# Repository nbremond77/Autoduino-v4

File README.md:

# Autoduino

Arduino DUE shield to interface the I/O modules of A4 Technology // Autoduino est un bouclier pour Arduino DUE qui permet de piloter les maquettes A4 Technology utilisées pour l'enseignement de la technologie. Il permet également d'interfacer des module Grove.

La face "Bottom":

La face "Top"

Exemples de maquettes A4:

http://www.a4.fr/maquette-motorisee-programmable-portail-1-battant-version-kit.html

http://www.a4.fr/banc-d-essai-eclairage-domestique-autolumi-version-kit.html

http://www.a4.fr/autoalarme-maquette-experimentale-d-un-systeme-d-alarme-kit.html

Vous trouverez sur ce site, les fichiers relatif à la carte électronique, et les développements logiciels associés, dès qu'ils seront disponibles. Cette carte peut être programmée en utilisant l'environnement Arduino. Mais elle peut également en programmée avec Blockly@rDuino, l'excellent projet de Sébastien Canet:

http://technologiescollege.github.io/Blockly-at-rduino/

https://github.com/technologiescollege/Blockly-at-rduino

# Introduction
Le bouclier Autoduino permet de piloter les maquettes A4 technology grâce à un Arduino DUE. Pour cela, le bouclier est équipé de 
- 14 connecteurs Jack 2.5mm permettant la connection des capteurs et actionneurs des maquette A4, équipé de LED pour indiquer l'état de l'entrée ou de la sortie. Des connecteurs Grove (4 broches) sont également prévus, et connectés aux mêmes entrées sorties (voir le schéma pour les détails). Les entrées sont équipées de résistances "Pull-Up" c'est à dire reliées à l'alimentation positive. Les entrées et sorties sont universelles (les schémas sont identiques), les 14 connections peuvent entre utilisées en entrée ou en sortie.
- 2 connecteurs jack 2.5mm pour deux moteurs DC, également complétés par des connecteurs Grove.
- 2 LED RGB adressables (type WS2812B),
- 1 encodeur/push,
- quelques connecteurs supplémentaires permettant de connecter des capteurs/actionneurs plus évolués (I2C, SPI, CAN, Serial...),
- 1 connecteur pour un module BlueTooth,
- 1 convertisseur Step/Up permettant d'alimenter la carte et l'Arduino avec deux piles de 1.5V, ou avec un accumulateur 3.7V,
- 1 connecteur pour un écran graphique couleur tactile de 2.8" connecté en SPI référencé TJCTM24028-SPI disponible pour un prix raisonnable sur Aliexpress.com.

Pour supporter le grand nombre d'entrées/sorties, il a été nécessaire d'utiliser un Arduino plus complet que le UNO. Nous avons choisi le Arduino DUE qui est équipé d'un processeur 32 bits permettant d'héberger des programmes trés complexes.

# Spécificités de l'Arduino DUE

L'Arduino DUE fonctionne en 3.3V, et n'est pas compatible avec des périphériques fonctionnant en 5V. Assurez vous que les périphériques utilisés fonctionnent bien en 3.3V. Les deux interface moteur prévues sur la carte Autoduino sont quant-à-elles alimentées en 5V.

# Schéma électronique

La conception du circuit imprimé a été réalisée avec kiCad, l'excellent logiciel de conception électronique, libre et multiplateforme. Le schéma est disponible ici:
https://github.com/nbremond77/Autoduino-v4/raw/master/Hardware/rev%204/Output/Autoduino-rev4.pdf

# Approvisionnement des composants

Les composants ont été achetés sur Aliepxress, et le PCb a été commandé chez PCBWay.com.

Voici des liens vers les principales références:

La carte Arduino DUE: https://fr.aliexpress.com/item/Free-shipping-Due-R3-ARM-Version-Main-Control-Board-with-usb-cable-for-arduino/32458422375.html?spm=2114.06010108.3.9.xlUYYH&ws_ab_test=searchweb0_0,searchweb201602_2_10152_10065_10151_10068_10305_10304_10306_10136_10137_10060_10302_10155_10062_437_10154_10056_5210020_10055_10054_10059_303_5290020_100031_10099_10103_10102_10096_10052_10053_10050_10107_10142_10051_5280011_10084_10083_10080_10082_10081_5260020_5270020_10177_5320020_10110_519_10111_10112_10113_10114_10182_10184_10078_10079_5240020_5230020_10073_10123_5250020_10189_142,searchweb201603_49,ppcSwitch_5&btsid=a1133e54-5694-44cb-906c-6a8b10082eb8&algo_expid=972c692f-a693-491d-9626-1f7036225856-1&algo_pvid=972c692f-a693-491d-9626-1f7036225856

Les connecteurs Jack 2.5mm CMS ref. PJ-242 : https://fr.aliexpress.com/item/500pcs-lot-PJ-242-6P-SMT-2-5MM-Female-Audio-Headphone-Jack-2-5MM-Dual-Track/32344264172.html?spm=2114.13010608.0.0.wAqt4l

L'écran LCD couleur tactile de 2.8" (attention, certains modèle ne sont pas équipés de l'interface tactile) : https://fr.aliexpress.com/item/2-8-Inch-240x320-Serial-Port-SPI-TFT-Screen-LCD-with-Touch-Screen-Panel-PCB-Board/32617643223.html?spm=2114.13010208.99999999.270.1LTJxa

Le module BlueTooth HC05 (les broches devront peut-être être déssoudées et remplacées par des barettes droites soudées sur la face inférieure) : https://fr.aliexpress.com/item/HC05-HC-05-master-slave-6pin-JY-MCU-anti-reverse-integrated-Bluetooth-serial-pass-through-module/32788718239.html?spm=2114.06010108.3.58.m5KIcO&ws_ab_test=searchweb0_0,searchweb201602_2_10152_10065_10151_10068_10305_10304_10306_10136_10137_10060_10302_10155_10062_437_10154_10056_5210020_10055_10054_10059_303_5290020_100031_10099_10103_10102_10096_10052_10053_10050_10107_10142_10051_5280011_10084_10083_10080_10082_10081_5260020_5270020_10177_5320020_10110_519_10111_10112_10113_10114_10182_10184_10078_10079_5240020_5230020_10073_10123_5250020_10189_142-10050,searchweb201603_49,ppcSwitch_5&btsid=7052be95-a9a1-4971-bb41-739faffda7ad&algo_expid=dd608b64-cccf-44a9-9c7e-1e9cdb78854b-7&algo_pvid=dd608b64-cccf-44a9-9c7e-1e9cdb78854b

Les autres composants sont des modèles standards.

# Circuit imprimé et fabrication

Autoduino utilise des composants CMS et des composants traversants. Le cuircuit imprimé fait 100x100mm et est du type double-face à trous métalisés. Nous l'avons fait fariqué chez PCBWay.com à un prix trés compétitif. Tous les fichiers nécessaires à sa fabrication sont dans le répertoire Output/Manufacturing (voir le fichier .Zip dans ce répertoire). Pensez également à commander un "Stencyl" pour la face "Bottom". Le Stencyl est un feuille de métal performée au laser au niveau des pastilles de soudure, et qui permet de grandement faciliter l'application de la pate à braser utilisée pour souder les  composants CMS.

Pour l'assemblage, de nombreux composants sont "montés en surface (CMS) sur la face "Bottom". Nous avons utilisé le Stencyl pour appliquer la pate à braser, positionné les composants CMS sur la carte, et passé la carte aisni équipé dans un four à refusion fait "maison" (plusieurs projets sont disponibles sur le web...).
Le montage des composants traversants, et des 2 LED sur la face "Top" se fait manuellement, aprés la refusion et le refroidissement de la carte. Cette méthode permet de réaliser plusieurs exemplaires de la carte en un temps raisonnable.

# Programmation
La programmation de l'Arduino peut se faire grâce à blockly@rDuino: http://technologiescollege.github.io/ en utilisant les blocs Grove par exemple.

http://technologiescollege.github.io/Blockly-at-rduino/

https://github.com/technologiescollege/Blockly-at-rduino

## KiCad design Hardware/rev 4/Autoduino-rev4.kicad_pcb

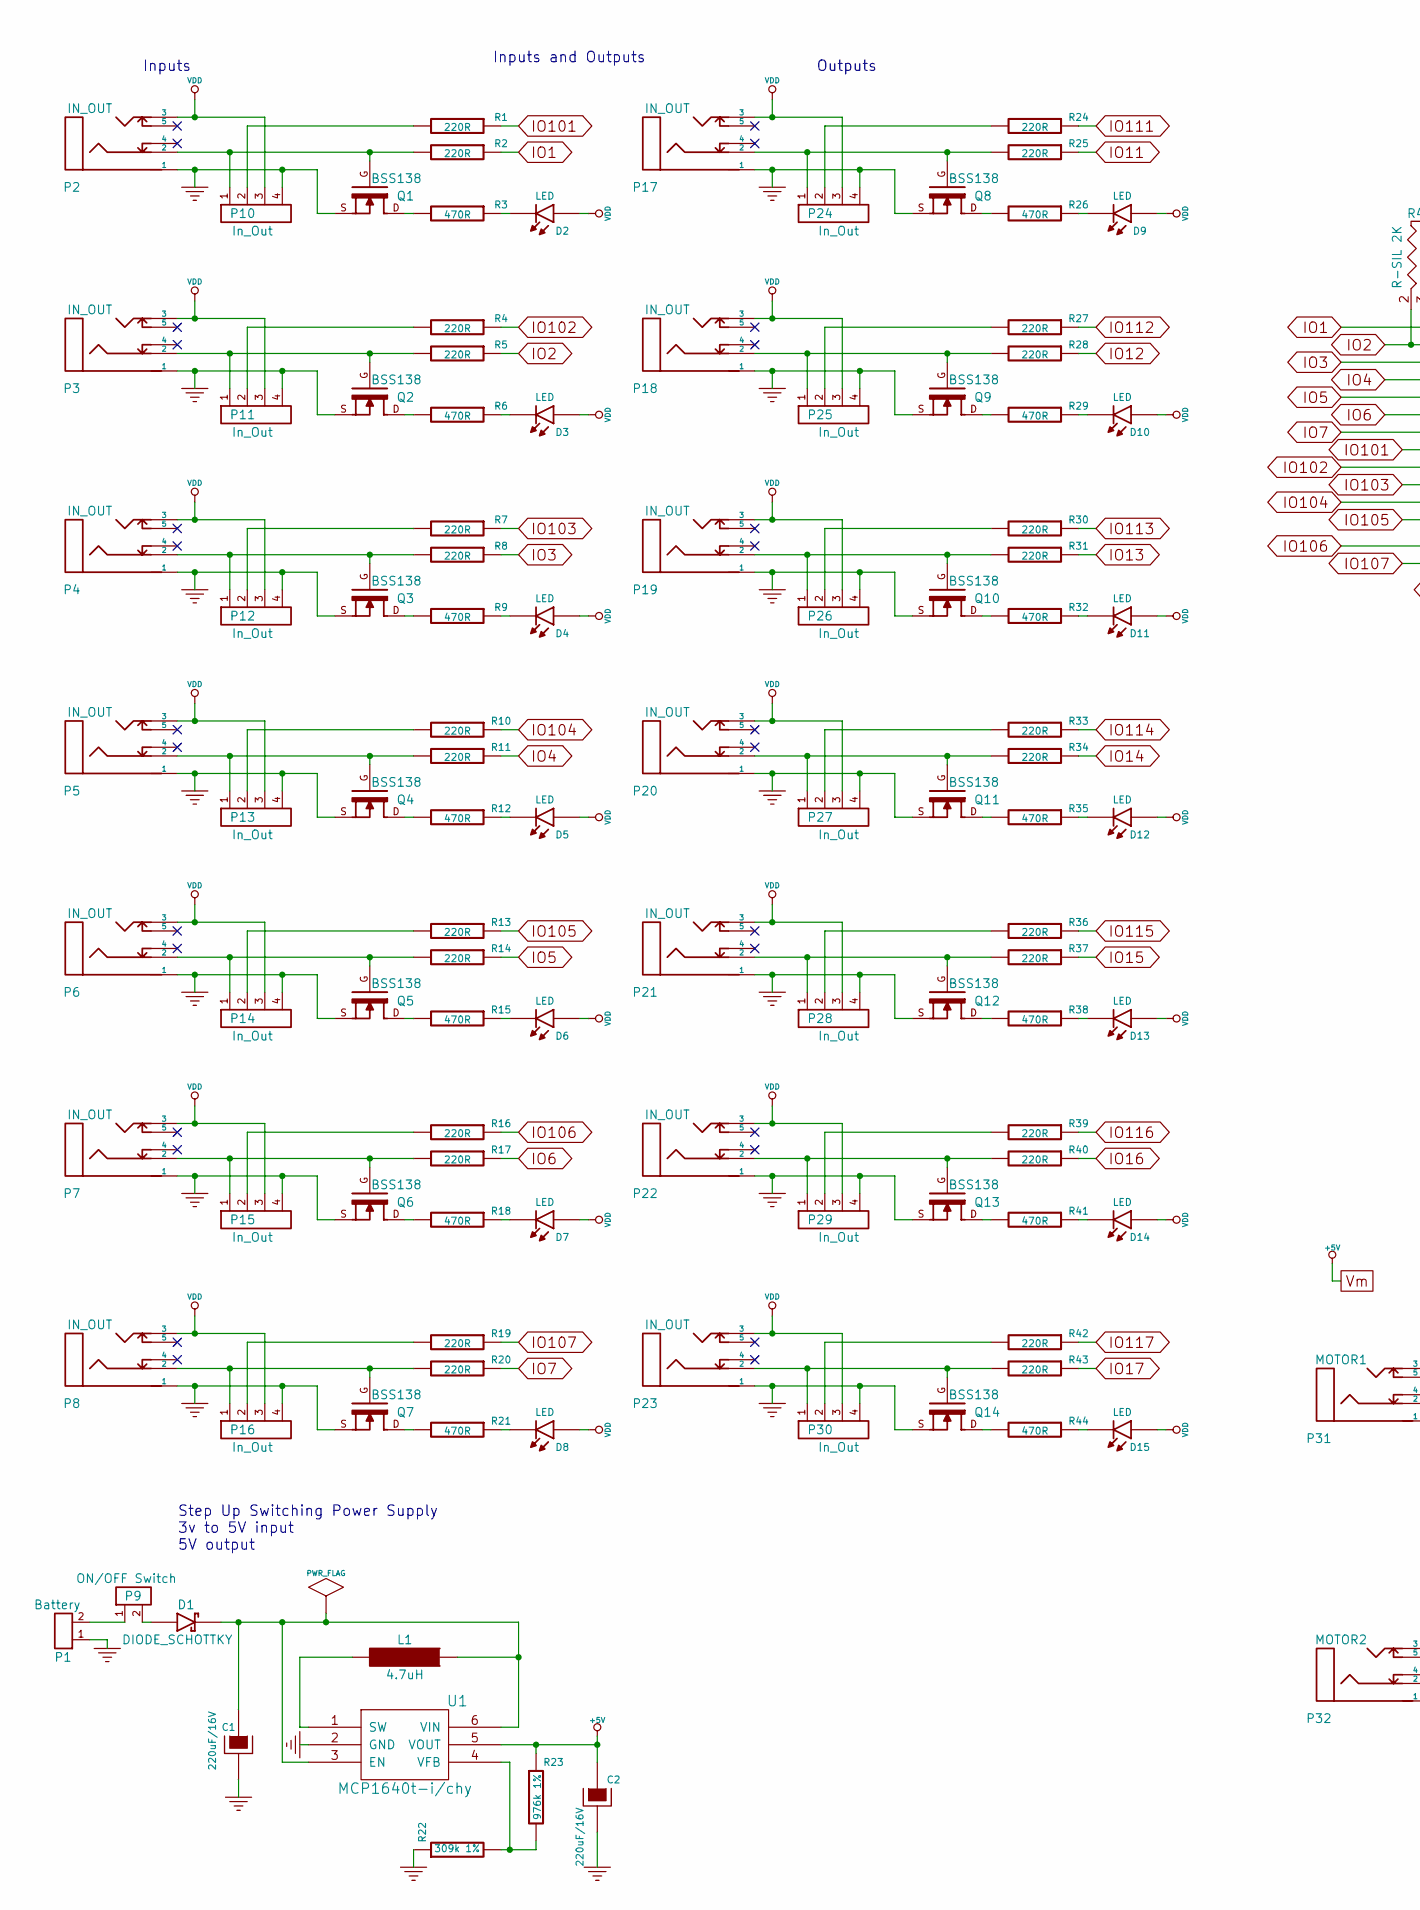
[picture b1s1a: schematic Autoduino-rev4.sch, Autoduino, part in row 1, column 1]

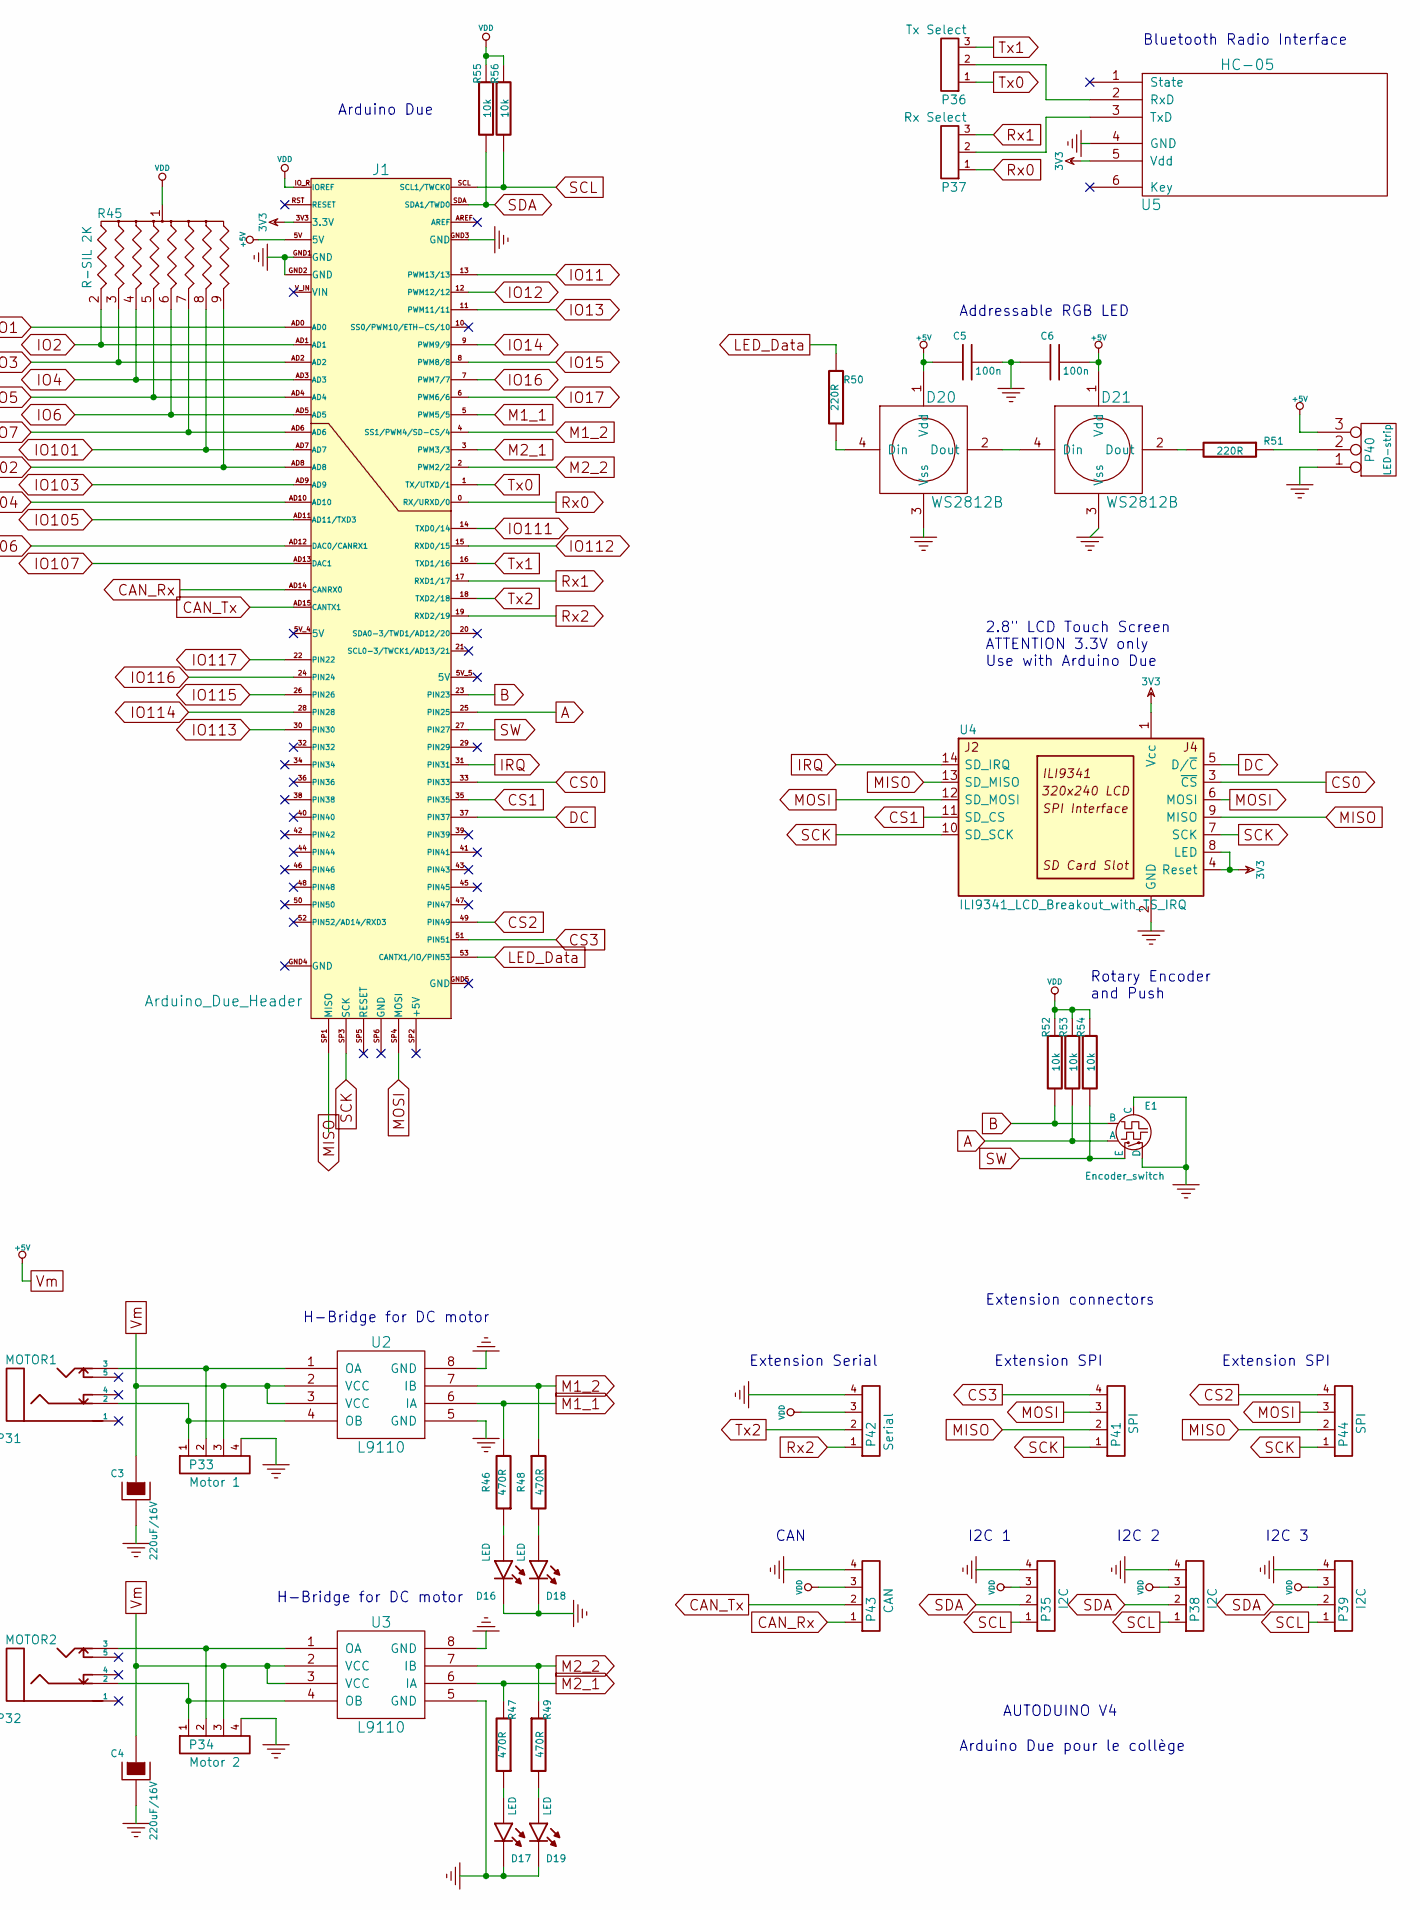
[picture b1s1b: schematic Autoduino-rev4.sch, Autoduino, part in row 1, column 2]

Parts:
C1, C2, C3, C4: 220uF/16V; CP_Elec_8x10
C5, C6: 100n; C_0805_HandSoldering
D1: DIODE_SCHOTTKY; D_MiniMELF_Handsoldering
D2, D3, D4, D5, D6, D7, D8, D9, D10, D11, D12, D13, D14, D15, D16, D17, D18, D19: LED; LED_D3.0mm
D20, D21: WS2812B; LED_WS2812B-PLCC4
E1: Encoder_switch; encoder_alps-ec12d
J1: Arduino_Due_Header; ARDUINO_MEGA_SHIELD
L1: 4.7uH; INDUCTOR_V
P1: Battery; Pin_Header_Straight_1x02_Pitch2.54mm
P2, P3, P4, P5, P6, P7, P8, P17, P18, P19, P20, P21, P22, P23: IN_OUT; 3.5mm_stereo_jack_PJ242_NBR
P9: ON/OFF Switch; Pin_Header_Straight_1x02_Pitch2.54mm
P10, P11, P12, P13, P14, P15, P16, P24, P25, P26, P27, P28, P29, P30: In_Out; Molex_MicroLatch-53253-0470_04x2.00mm_Straight
P31: MOTOR1; 3.5mm_stereo_jack_PJ242_NBR
P32: MOTOR2; 3.5mm_stereo_jack_PJ242_NBR
P33: Motor 1; Molex_MicroLatch-53253-0470_04x2.00mm_Straight
P34: Motor 2; Molex_MicroLatch-53253-0470_04x2.00mm_Straight
P35, P38, P39: I2C; Molex_MicroLatch-53253-0470_04x2.00mm_Straight
P36: Tx Select; Pin_Header_Straight_1x03_Pitch2.54mm
P37: Rx Select; Pin_Header_Straight_1x03_Pitch2.54mm
P40: LED-strip; Pin_Header_Straight_1x03_Pitch2.54mm
P41, P44: SPI; Molex_MicroLatch-53253-0470_04x2.00mm_Straight
P42: Serial; Molex_MicroLatch-53253-0470_04x2.00mm_Straight
P43: CAN; Molex_MicroLatch-53253-0470_04x2.00mm_Straight
Q1, Q2, Q3, Q4, Q5, Q6, Q7, Q8, Q9, Q10, Q11, Q12, Q13, Q14: BSS138; SOT23_FET
R1, R2, R4, R5, R7, R8, R10, R11, R13, R14, R16, R17, R19, R20, R24, R25, R27, R28, R30, R31, R33, R34, R36, R37, R39, R40, R42, R43, R50, R51: 220R; R_0805_HandSoldering
R3, R6, R9, R12, R15, R18, R21, R26, R29, R32, R35, R38, R41, R44, R46, R47, R48, R49: 470R; R_0805_HandSoldering
R22: 309k 1%; R_0805_HandSoldering
R23: 976k 1%; R_0805_HandSoldering
R45: R-SIL 2K; R_Array_SIP9
R52, R53, R54, R55, R56: 10k; R_0805_HandSoldering
U1: MCP1640t-i/chy; SOT-23-6_Handsoldering
U2, U3: L9110; SOIC-8_3.9x4.9mm_Pitch1.27mm
U4: ILI9341_LCD_Breakout_with_TS_IRQ; LCD_2.8_Touch_screen
U5: HC-05; Pin_Header_Angled_1x06_Pitch2.54mm

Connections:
3V3: J1.3V3 (3.3V), U4.1 (Vcc), U4.4 (Reset), U4.8 (LED), U5.5 (Vdd)
A: E1.1 (A), J1.25 (PIN25), R53.2
B: E1.3 (B), J1.23 (PIN23), R52.2
CAN_Rx: J1.AD14 (CANRX0), P43.1
CAN_Tx: J1.AD15 (CANTX1), P43.2
CS0: J1.33 (PIN33), U4.3 (~CS)
CS1: J1.35 (PIN35), U4.11 (SD_CS)
CS2: J1.49 (PIN49), P44.4
CS3: J1.51 (PIN51), P41.4
DC: J1.37 (PIN37), U4.5 (D/~C)
GND: C1.2, C2.2, C3.2, C4.2, C5.2, C6.1, D16.2 (K), D17.2 (K), D18.2 (K), D19.2 (K), D20.3 (Vss), D21.3 (Vss), E1.2 (C), E1.5 (D), J1.GND1 (GND), J1.GND2 (GND), J1.GND3 (GND), P1.1, P2.1, P3.1, P4.1, P5.1, P6.1, P7.1, P8.1, P10.4, P11.4, P12.4, P13.4, P14.4, P15.4, P16.4, P17.1, P18.1, P19.1, P20.1, P21.1, P22.1, P23.1, P24.4, P25.4, P26.4, P27.4, P28.4, P29.4, P30.4, P33.4, P34.4, P35.4, P38.4, P39.4, P40.1, P42.4, P43.4, Q1.S, Q2.S, Q3.S, Q4.S, Q5.S, Q6.S, Q7.S, Q8.S, Q9.S, Q10.S, Q11.S, Q12.S, Q13.S, Q14.S, R22.1, U1.2 (GND), U2.5 (GND), U2.8 (GND), U3.5 (GND), U3.8 (GND), U4.2 (GND), U5.4 (GND)
IO1: J1.AD0, R2.1
IO2: J1.AD1, R5.1, R45.2
IO3: J1.AD2, R8.1, R45.3
IO4: J1.AD3, R11.1, R45.4
IO5: J1.AD4, R14.1, R45.5
IO6: J1.AD5, R17.1, R45.6
IO7: J1.AD6, R20.1, R45.7
IO11: J1.13 (PWM13/13), R25.1
IO12: J1.12 (PWM12/12), R28.1
IO13: J1.11 (PWM11/11), R31.1
IO14: J1.9 (PWM9/9), R34.1
IO15: J1.8 (PWM8/8), R37.1
IO16: J1.7 (PWM7/7), R40.1
IO17: J1.6 (PWM6/6), R43.1
IO101: J1.AD7, R1.1, R45.8
IO102: J1.AD8, R4.1, R45.9
IO103: J1.AD9, R7.1
IO104: J1.AD10, R10.1
IO105: J1.AD11 (AD11/TXD3), R13.1
IO106: J1.AD12 (DAC0/CANRX1), R16.1
IO107: J1.AD13 (DAC1), R19.1
IO111: J1.14 (TXD0/14), R24.1
IO112: J1.15 (RXD0/15), R27.1
IO113: J1.30 (PIN30), R30.1
IO114: J1.28 (PIN28), R33.1
IO115: J1.26 (PIN26), R36.1
IO116: J1.24 (PIN24), R39.1
IO117: J1.22 (PIN22), R42.1
IRQ: J1.31 (PIN31), U4.14 (SD_IRQ)
LED_Data: J1.53 (CANTX1/IO/PIN53), R50.2
M1_1: J1.5 (PWM5/5), R46.2, U2.6 (IA)
M1_2: J1.4 (SS1/PWM4/SD-CS/4), R48.1, U2.7 (IB)
M2_1: J1.3 (PWM3/3), R47.2, U3.6 (IA)
M2_2: J1.2 (PWM2/2), R49.1, U3.7 (IB)
MISO: J1.SP1 (MISO), P41.2, P44.2, U4.9 (MISO), U4.13 (SD_MISO)
MOSI: J1.SP4 (MOSI), P41.3, P44.3, U4.6 (MOSI), U4.12 (SD_MOSI)
unnamed: C1.1, D1.2 (K), L1.1, U1.3 (EN), U1.6 (VIN)
unnamed: D1.1 (A), P9.2
unnamed: D2.2 (K), R3.1
unnamed: D3.2 (K), R6.1
unnamed: D4.2 (K), R9.1
unnamed: D5.2 (K), R12.1
unnamed: D6.2 (K), R15.1
unnamed: D7.2 (K), R18.1
unnamed: D8.2 (K), R21.1
unnamed: D9.2 (K), R26.1
unnamed: D10.2 (K), R29.1
unnamed: D11.2 (K), R32.1
unnamed: D12.2 (K), R35.1
unnamed: D13.2 (K), R38.1
unnamed: D14.2 (K), R41.1
unnamed: D15.2 (K), R44.1
unnamed: D16.1 (A), R46.1
unnamed: D17.1 (A), R47.1
unnamed: D18.1 (A), R48.2
unnamed: D19.1 (A), R49.2
unnamed: D20.2 (Dout), D21.4 (Din)
unnamed: D20.4 (Din), R50.1
unnamed: D21.2 (Dout), R51.2
unnamed: L1.2, U1.1 (SW)
unnamed: P1.2, P9.1
unnamed: P2.2, P10.1, Q1.G, R2.2
unnamed: P10.2, R1.2
unnamed: P3.2, P11.1, Q2.G, R5.2
unnamed: P11.2, R4.2
unnamed: P4.2, P12.1, Q3.G, R8.2
unnamed: P12.2, R7.2
unnamed: P5.2, P13.1, Q4.G, R11.2
unnamed: P13.2, R10.2
unnamed: P6.2, P14.1, Q5.G, R14.2
unnamed: P14.2, R13.2
unnamed: P7.2, P15.1, Q6.G, R17.2
unnamed: P15.2, R16.2
unnamed: P8.2, P16.1, Q7.G, R20.2
unnamed: P16.2, R19.2
unnamed: P17.2, P24.1, Q8.G, R25.2
unnamed: P18.2, P25.1, Q9.G, R28.2
unnamed: P19.2, P26.1, Q10.G, R31.2
unnamed: P20.2, P27.1, Q11.G, R34.2
unnamed: P21.2, P28.1, Q12.G, R37.2
unnamed: P22.2, P29.1, Q13.G, R40.2
unnamed: P23.2, P30.1, Q14.G, R43.2
unnamed: P24.2, R24.2
unnamed: P25.2, R27.2
unnamed: P26.2, R30.2
unnamed: P27.2, R33.2
unnamed: P28.2, R36.2
unnamed: P29.2, R39.2
unnamed: P30.2, R42.2
unnamed: P31.2, P33.1, U2.4 (OB)
unnamed: P31.3, P33.2, U2.1 (OA)
unnamed: P32.2, P34.1, U3.4 (OB)
unnamed: P32.3, P34.2, U3.1 (OA)
unnamed: P36.2, U5.2 (RxD)
unnamed: P37.2, U5.3 (TxD)
unnamed: P40.2 (PM), R51.1
unnamed: Q1.D, R3.2
unnamed: Q2.D, R6.2
unnamed: Q3.D, R9.2
unnamed: Q4.D, R12.2
unnamed: Q5.D, R15.2
unnamed: Q6.D, R18.2
unnamed: Q7.D, R21.2
unnamed: Q8.D, R26.2
unnamed: Q9.D, R29.2
unnamed: Q10.D, R32.2
unnamed: Q11.D, R35.2
unnamed: Q12.D, R38.2
unnamed: Q13.D, R41.2
unnamed: Q14.D, R44.2
unnamed: R22.2, R23.2, U1.4 (VFB)
Rx0: J1.0 (RX/URXD/0), P37.1
Rx1: J1.17 (RXD1/17), P37.3
Rx2: J1.19 (RXD2/19), P42.1
SCK: J1.SP3 (SCK), P41.1, P44.1, U4.7 (SCK), U4.10 (SD_SCK)
SCL: J1.SCL (SCL1/TWCK0), P35.1, P38.1, P39.1, R56.2
SDA: J1.SDA (SDA1/TWD0), P35.2, P38.2, P39.2, R55.2
SW: E1.4 (E), J1.27 (PIN27), R54.2
Tx0: J1.1 (TX/UTXD/1), P36.1
Tx1: J1.16 (TXD1/16), P36.3
Tx2: J1.18 (TXD2/18), P42.2
VDD: D2.1 (A), D3.1 (A), D4.1 (A), D5.1 (A), D6.1 (A), D7.1 (A), D8.1 (A), D9.1 (A), D10.1 (A), D11.1 (A), D12.1 (A), D13.1 (A), D14.1 (A), D15.1 (A), J1.IO_R (IOREF), P2.3, P3.3, P4.3, P5.3, P6.3, P7.3, P8.3, P10.3, P11.3, P12.3, P13.3, P14.3, P15.3, P16.3, P17.3, P18.3, P19.3, P20.3, P21.3, P22.3, P23.3, P24.3, P25.3, P26.3, P27.3, P28.3, P29.3, P30.3, P35.3, P38.3, P39.3, P42.3, P43.3, R45.1, R52.1, R53.1, R54.1, R55.1, R56.1
Vm: C2.1, C3.1, C4.1, C5.1, C6.2, D20.1 (Vdd), D21.1 (Vdd), J1.5V, P33.3, P34.3, P40.3, R23.1, U1.5 (VOUT), U2.2 (VCC), U2.3 (VCC), U3.2 (VCC), U3.3 (VCC)

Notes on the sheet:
Bluetooth Radio Interface
Addressable RGB LED
H-Bridge for DC motor
I2C 3
Rotary Encoder and Push
Extension connectors
I2C 2
I2C 1
2.8" LCD Touch Screen ATTENTION 3.3V only Use with Arduino Due
Inputs and Outputs
Arduino Due
AUTODUINO V4
Arduino Due pour le collège
Step Up Switching Power Supply 3v to 5V input 5V output
Extension SPI
Inputs
Outputs
Extension Serial
CAN

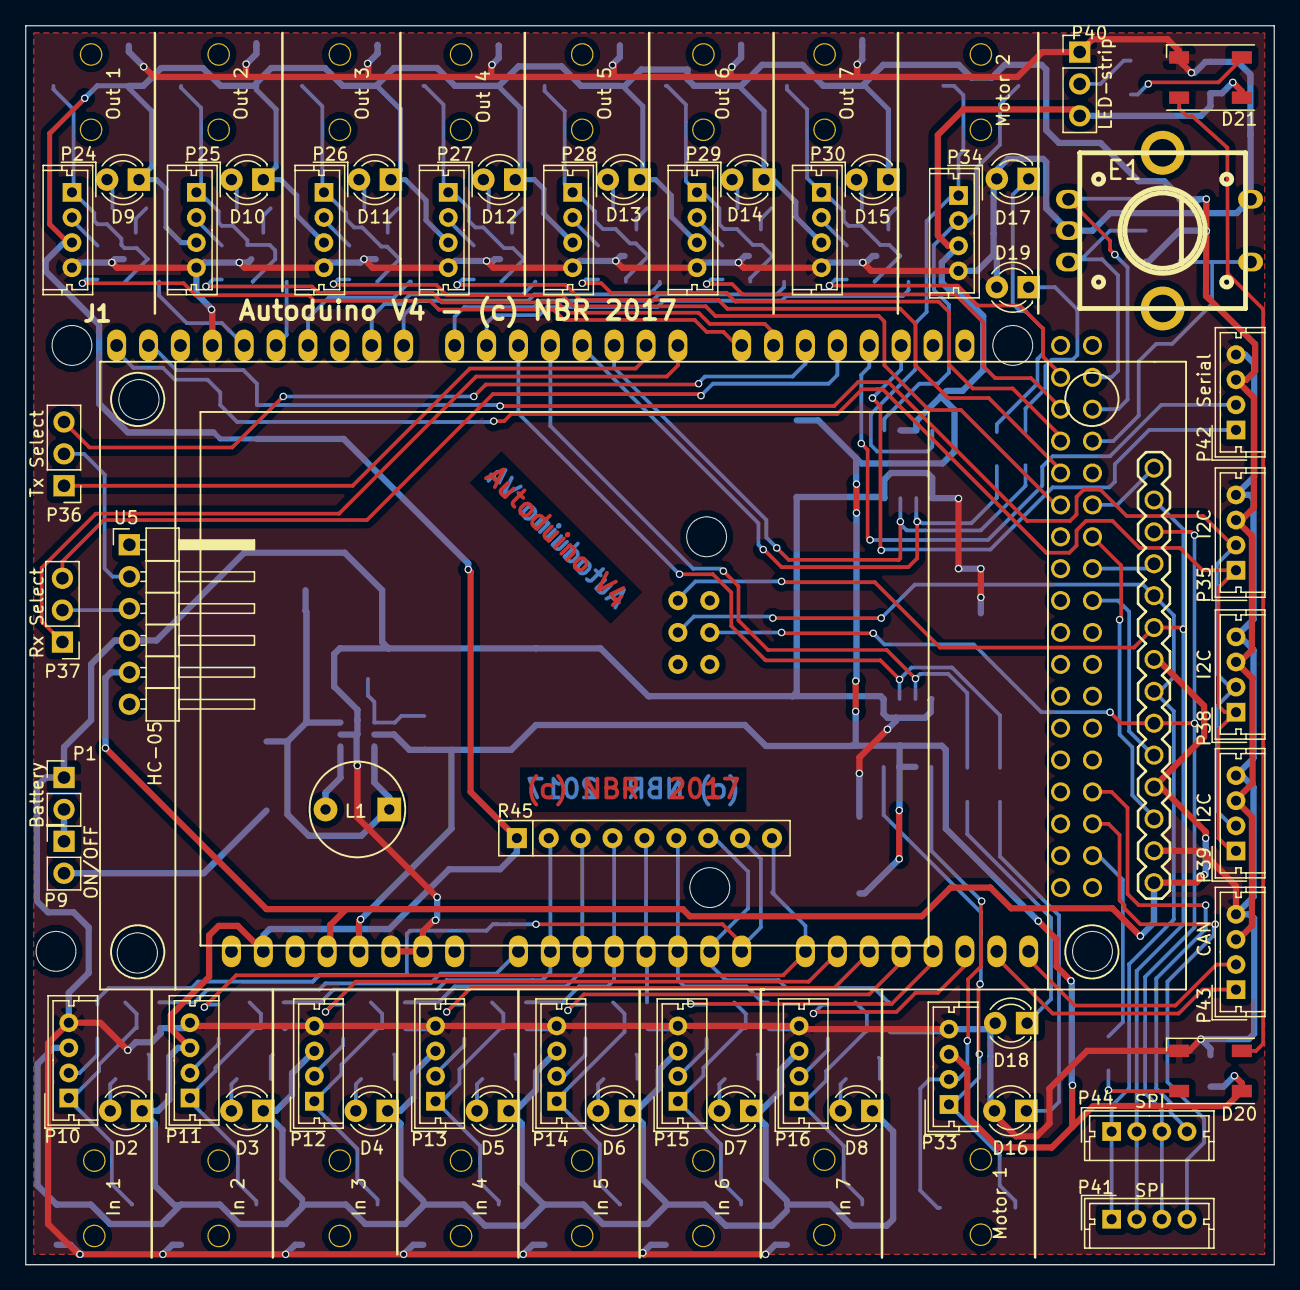
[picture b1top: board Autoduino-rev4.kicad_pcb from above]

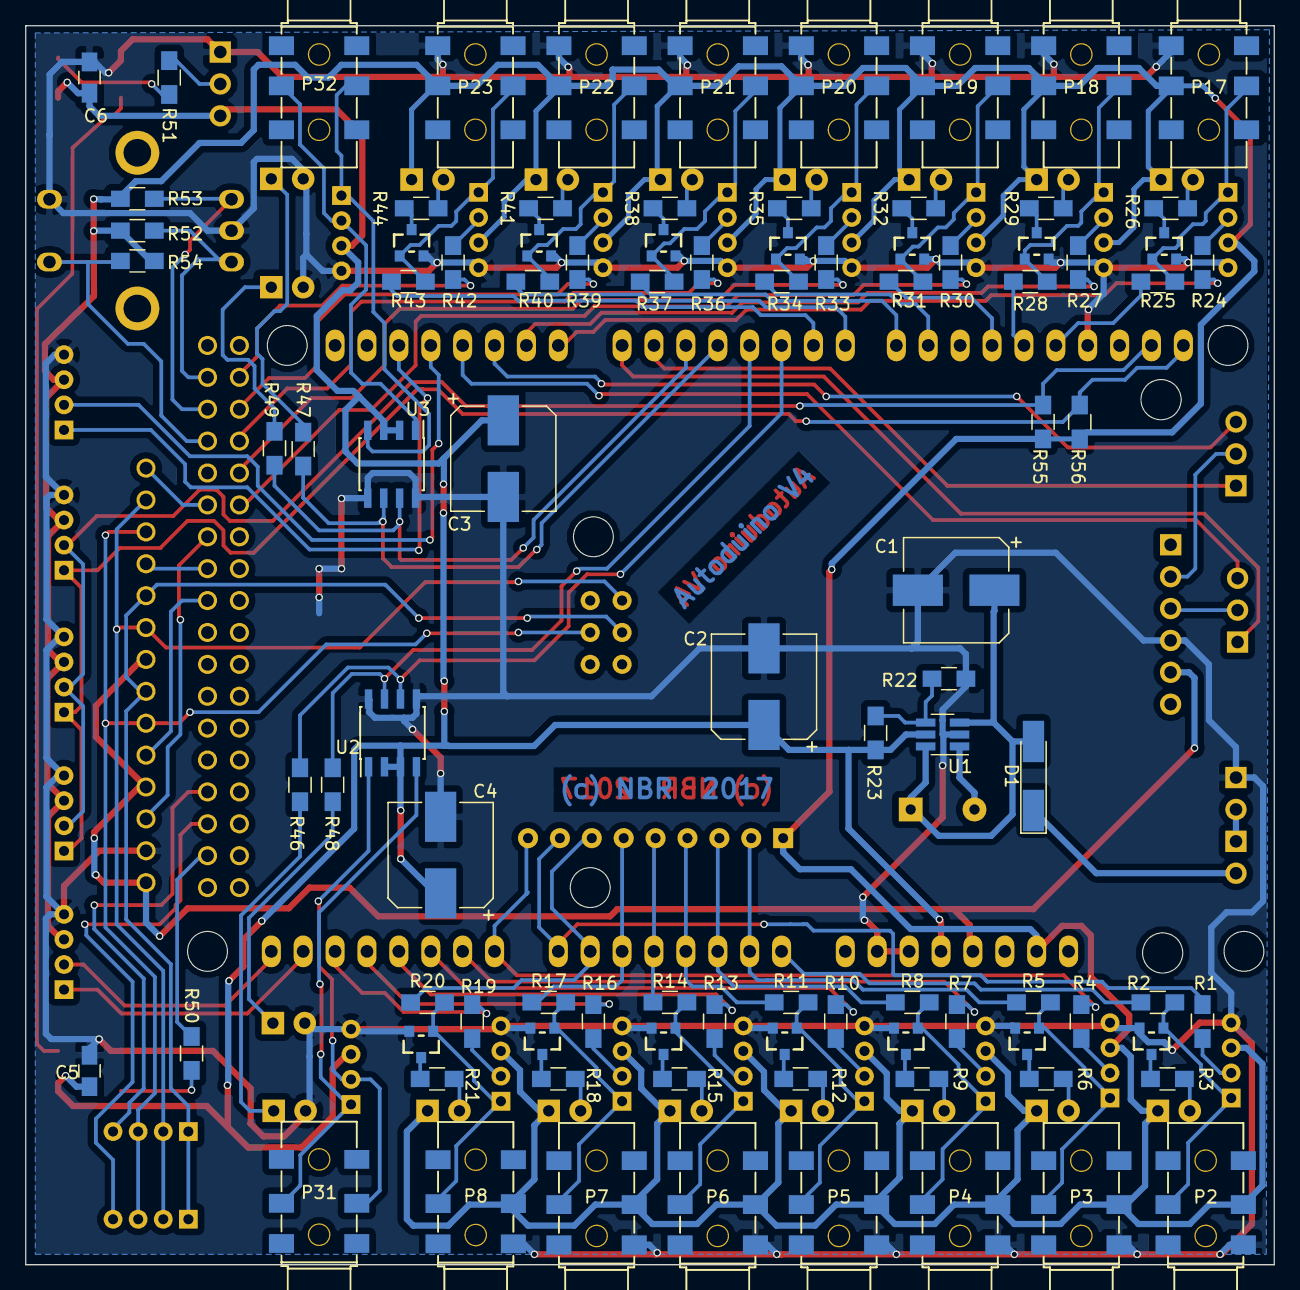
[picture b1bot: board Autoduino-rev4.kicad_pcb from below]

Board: 2 copper layers, 99.4 x 98.7 mm, 149 parts (95 on the bottom side), 134 nets.

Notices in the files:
Hardware/rev 4/Autoduino-rev4.sch:
Open hardware Licence
